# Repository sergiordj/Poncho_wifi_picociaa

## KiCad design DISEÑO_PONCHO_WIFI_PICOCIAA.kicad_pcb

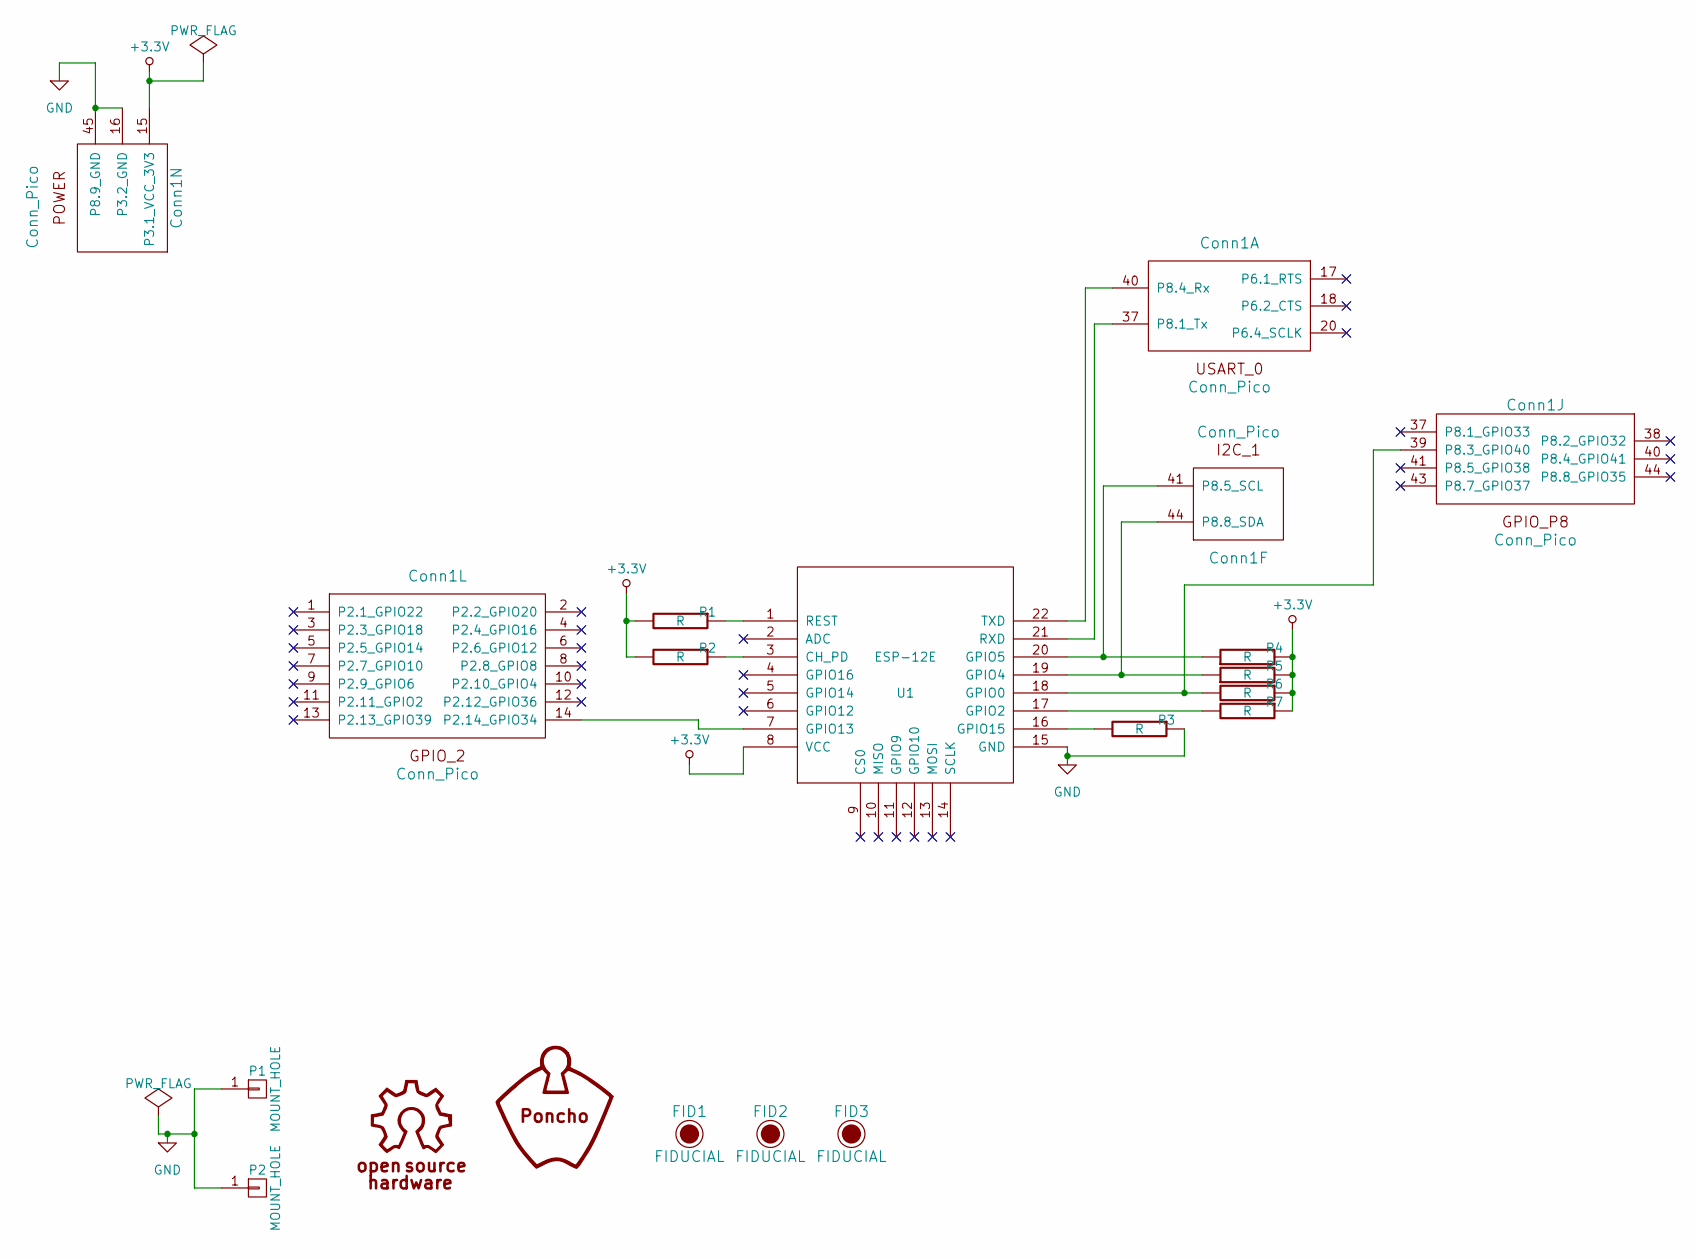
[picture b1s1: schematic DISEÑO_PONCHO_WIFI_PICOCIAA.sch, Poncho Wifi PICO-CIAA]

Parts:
Conn1: Conn_Pico; Conn_Pico_Ciaa; Digikey# Value
FID1, FID2, FID3: FIDUCIAL; Fiducial_1mm_Dia_2.54mm_Outer_CopperTop
P1, P2: MOUNT_HOLE; PIN_ARRAY_1
R1, R2, R3, R4, R5, R6, R7: R; R_0805_HandSoldering; Digikey# 1056-MCR10J103-CHP
U1: ESP-12E; Digikey# 1528-1438-ND

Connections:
+3.3V: Conn1.15 (P3.1_VCC_3V3), R1.2, R2.2, R4.2, R5.2, R6.1, R7.1, U1.8 (VCC)
GND: Conn1.16 (P3.2_GND), Conn1.45 (P8.9_GND), P1.1, P2.1, R3.1, U1.15 (GND)
unnamed: Conn1.14 (P2.14_GPIO34), U1.7 (GPIO13)
unnamed: Conn1.37 (P8.1_Tx), U1.21 (RXD)
unnamed: Conn1.39 (P8.3_SCL), R6.2, U1.18 (GPIO0)
unnamed: Conn1.40 (P8.4_Rx), U1.22 (TXD)
unnamed: Conn1.41 (P8.5_CTS), R4.1, U1.20 (GPIO5)
unnamed: Conn1.44 (P8.8_SDA), R5.1, U1.19 (GPIO4)
unnamed: R1.1, U1.1 (REST)
unnamed: R2.1, U1.3 (CH_PD)
unnamed: R3.2, U1.16 (GPIO15)
unnamed: R7.2, U1.17 (GPIO2)

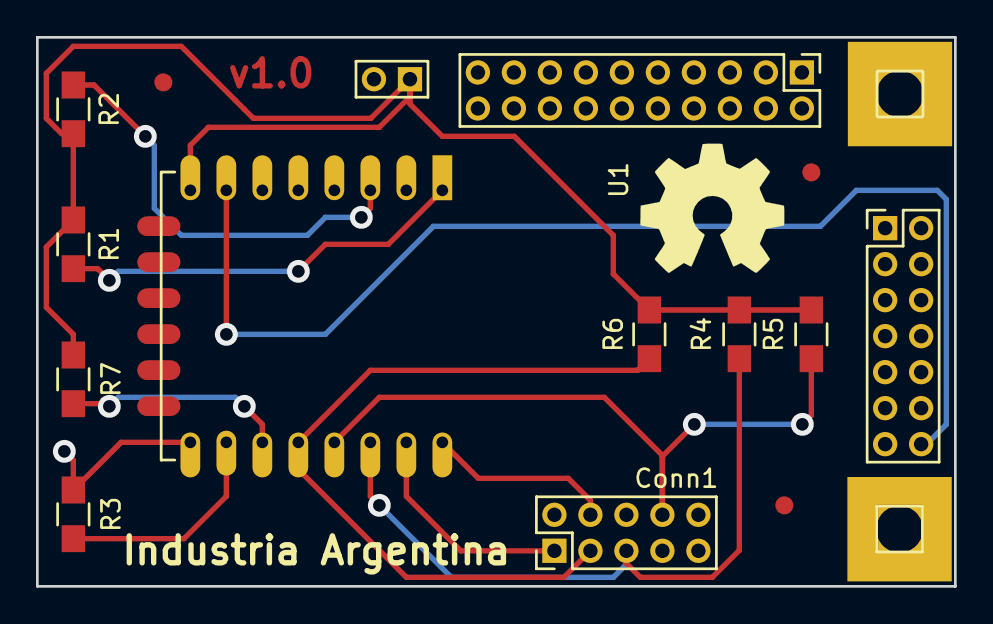
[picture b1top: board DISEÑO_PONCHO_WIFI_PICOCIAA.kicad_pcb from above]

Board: 2 copper layers, 51.0 x 30.5 mm, 15 parts (0 on the bottom side), 12 nets.

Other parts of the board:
G101: Logo_OSHWA

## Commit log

2016-12-19 Comentarios DB
2016-12-19 Footprints locales
2016-12-20 Ruteo y limpieza de proyecto
2016-12-20 Ruteo y limpoeza del proyecto
2016-12-20 Limpieza de bibliotecas
2016-12-21 Se introducen comentarios de SL
2016-12-28 reparacion de bibliotecas
2016-12-28 Reparacion de biblioteca
